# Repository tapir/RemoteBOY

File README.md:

Mechanical Files: https://cad.onshape.com/documents/e0ada551acd8132e7ef75c1d/w/a94723651199e5762ecd29c6/e/211c17ef0ce3b004e12369c1?renderMode=0&uiState=660063c5c1c4d963c4f33858

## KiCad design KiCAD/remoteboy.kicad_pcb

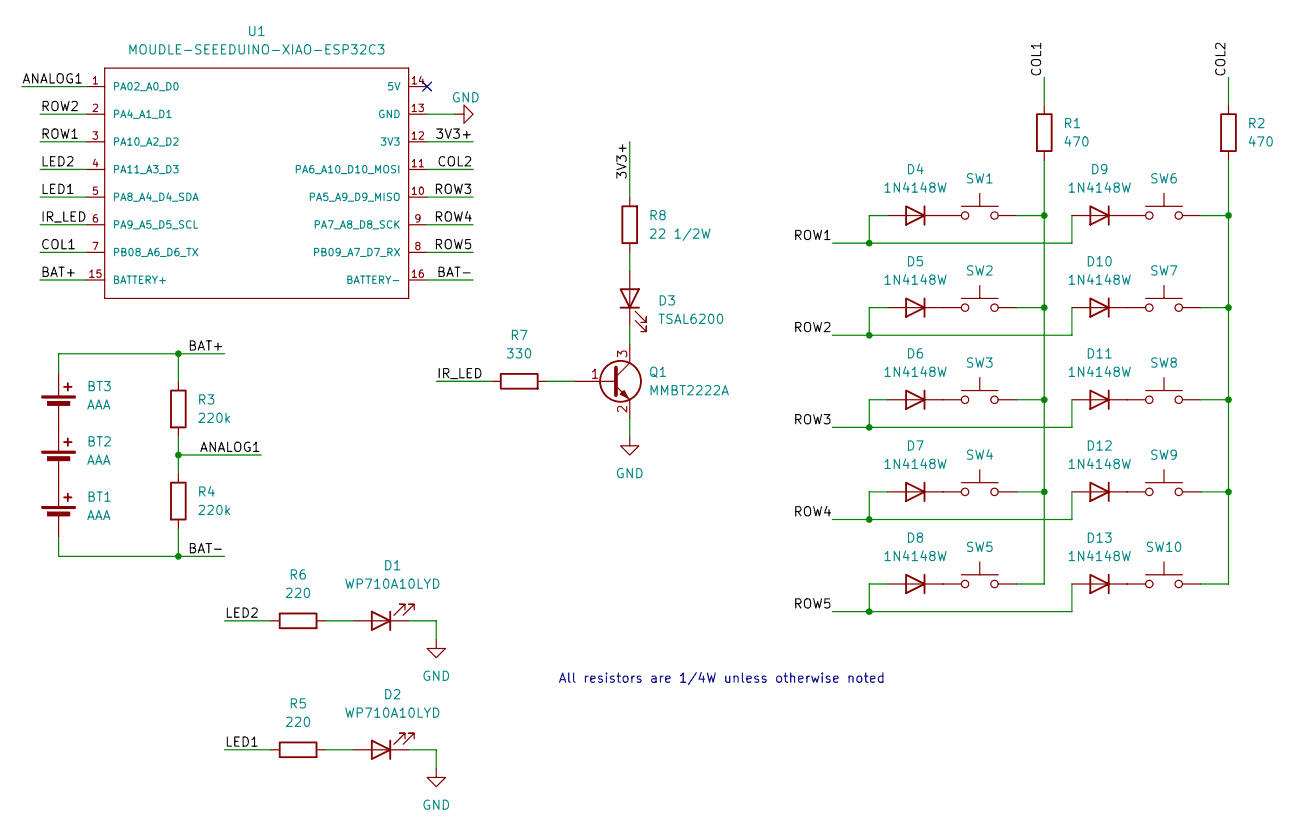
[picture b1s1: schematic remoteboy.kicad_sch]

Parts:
BT1, BT2, BT3: AAA; BAT_1020
D1, D2: WP710A10LYD; LED_D3.0mm
D3: TSAL6200; LED_D5.0mm
D4, D5, D6, D7, D8, D9, D10, D11, D12, D13: 1N4148W; D_SOD-123
Q1: MMBT2222A; SOT-23
R1, R2: 470; R_0805_2012Metric
R3, R4: 220k; R_0805_2012Metric
R5, R6: 220; R_0805_2012Metric
R7: 330; R_0805_2012Metric
R8: 22 1/2W; R_0805_2012Metric
SW1, SW2, SW3, SW4, SW5, SW6, SW7, SW8, SW9, SW10: SW_Push; SiliconeDome
U1: MOUDLE-SEEEDUINO-XIAO-ESP32C3; MOUDLE14P-SMD-2.54-21X17.8MM

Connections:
/3V3+: R8.2, U1.12 (3V3)
/ANALOG1: R3.2, R4.1, U1.1 (PA02_A0_D0)
/BAT+: BT3.1 (+), R3.1, U1.15 (BATTERY+)
/BAT-: BT1.2 (-), R4.2, U1.16 (BATTERY-)
/COL1: R1.1, U1.7 (PB08_A6_D6_TX)
/COL2: R2.1, U1.11 (PA6_A10_D10_MOSI)
/IR_LED: R7.1, U1.6 (PA9_A5_D5_SCL)
/LED1: R5.1, U1.5 (PA8_A4_D4_SDA)
/LED2: R6.1, U1.4 (PA11_A3_D3)
/ROW1: D4.2 (A), D9.2 (A), U1.3 (PA10_A2_D2)
/ROW2: D5.2 (A), D10.2 (A), U1.2 (PA4_A1_D1)
/ROW3: D6.2 (A), D11.2 (A), U1.10 (PA5_A9_D9_MISO)
/ROW4: D7.2 (A), D12.2 (A), U1.9 (PA7_A8_D8_SCK)
/ROW5: D8.2 (A), D13.2 (A), U1.8 (PB09_A7_D7_RX)
GND: D1.1 (K), D2.1 (K), Q1.2 (E), U1.13 (GND)
unnamed: BT1.1 (+), BT2.2 (-)
unnamed: BT2.1 (+), BT3.2 (-)
unnamed: D1.2 (A), R6.2
unnamed: D2.2 (A), R5.2
unnamed: D3.2 (A), R8.1
unnamed: D3.1 (K), Q1.3 (C)
unnamed: D4.1 (K), SW1.1
unnamed: D5.1 (K), SW2.1
unnamed: D6.1 (K), SW3.1
unnamed: D7.1 (K), SW4.1
unnamed: D8.1 (K), SW5.1
unnamed: D9.1 (K), SW6.1
unnamed: D10.1 (K), SW7.1
unnamed: D11.1 (K), SW8.1
unnamed: D12.1 (K), SW9.1
unnamed: D13.1 (K), SW10.1
unnamed: Q1.1 (B), R7.2
unnamed: R1.2, SW1.2, SW2.2, SW3.2, SW4.2, SW5.2
unnamed: R2.2, SW6.2, SW7.2, SW8.2, SW9.2, SW10.2

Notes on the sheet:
All resistors are 1/4W unless otherwise noted

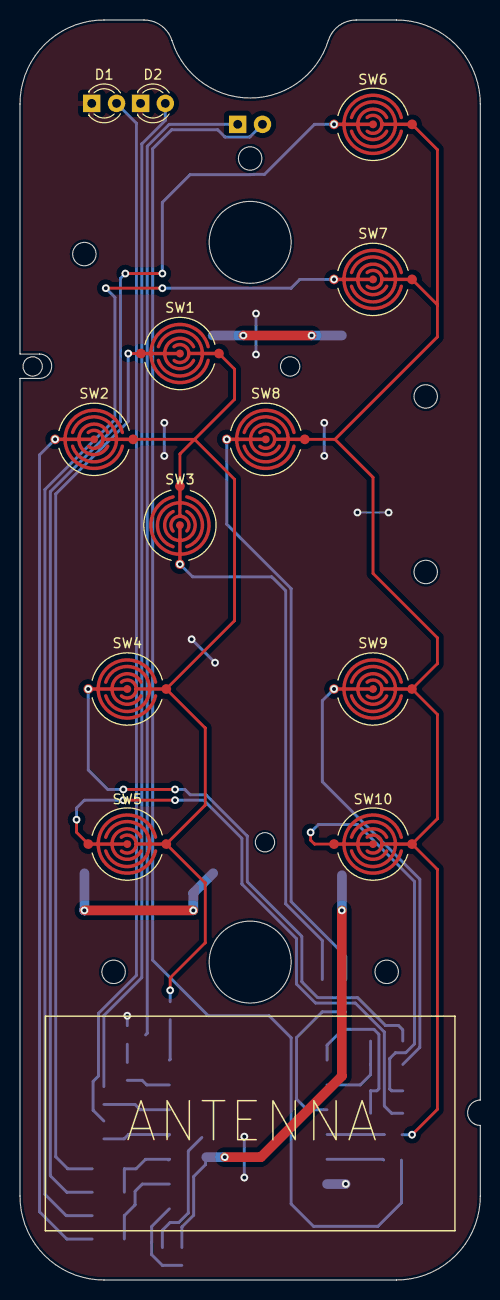
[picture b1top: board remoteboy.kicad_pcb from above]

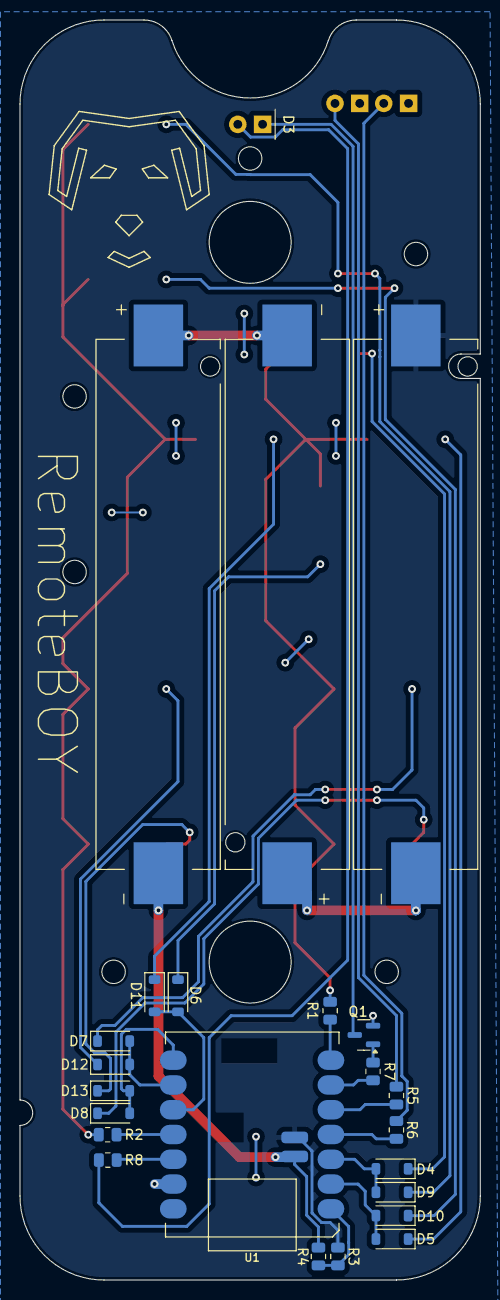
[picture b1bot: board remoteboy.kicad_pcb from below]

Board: 2 copper layers, 47.2 x 129.2 mm, 36 parts (24 on the bottom side), 34 nets.

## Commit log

2024-03-24 KiCAD files
2024-03-24 Readme
2024-03-24 Software
2024-03-24 Arduino folder structure
2024-03-24 Fix board thickness
2024-03-24 Update 3D
2024-03-24 Fix antenna silkscreen size
2024-03-24 Initial pin setup
2024-03-24 More definitions
2024-03-30 Initial software
2024-03-30 Clean a track
2024-03-30 Small fixes
2024-03-30 Implement LEDs
2024-03-30 Minor fixes
2024-03-31 Clang format
2024-03-31 Disable logging
2024-03-31 Fix spacing
2024-03-31 Update gitignore
2024-03-31 Remove kicad prl
2024-03-31 Carry battery level logic inside BLE class
2024-03-31 Initial layer and button logic
2024-03-31 Bug fixes
2024-03-31 Complete all LED states
2024-03-31 Implement IR
2024-03-31 Change delay position
2024-03-31 Remove var
2024-04-01 Fix IR code size
2024-04-01 IR implementation with non blocking repeat
2024-04-01 Remove unused var
2024-04-01 Coımments
2024-04-01 Comments
2024-04-01 Run IR repeat
2024-04-01 Fix repeat check
2024-04-01 Layout
2024-04-01 Typedef name
2024-04-01 Fix bluetooth pairing mode
2024-04-01 Move const
2024-04-01 IR implementation with non blocking repeat (#1)
    * IR implementation with non blocking repeat
    * Remove unused var
    * Coımments
    * Comments
    * Run IR repeat
    * Fix repeat check
2024-04-01 Add missin include
2024-04-02 LED fixes
2024-04-02 Fix battery
2024-04-02 Revert back frequency battery
2024-04-02 Fix schematic and pcb
2024-04-03 Battery correction factor
2024-04-03 Button handling changes
2024-04-04 Remove IR
2024-04-04 Remove IR, fix buttons, fix LEDs
2024-04-04 remove debugging messages
2024-04-04 Remove select from special buttons
2024-04-05 Add menu button
2024-04-05 Fix hid descriptor
2024-04-05 Remove BT disconnect
2024-04-05 Power management
2024-04-05 Disable serial
2024-04-05 Remove unnecessary
2024-04-05 Organize
2024-04-05 Clean includes
2024-04-06 Faster bluetooh reconnect
2024-04-06 Faster BT reconnect
2024-04-06 Fix gpio hold
2024-04-06 Clean BT before restart
2024-04-06 Fixes
2024-04-06 Disconnect BT before sleep
2024-04-07 Fix namings and organization
2024-04-07 Switch to edge trigger debounce
2024-04-07 Overhaul for wkaup button catch
2024-04-15 ESPNow implementation
2024-04-16 Overhaul
2024-04-16 Remove BLE
2024-04-16 Rename stuff
2024-04-16 Power management done. 0.3mA on sleep.
